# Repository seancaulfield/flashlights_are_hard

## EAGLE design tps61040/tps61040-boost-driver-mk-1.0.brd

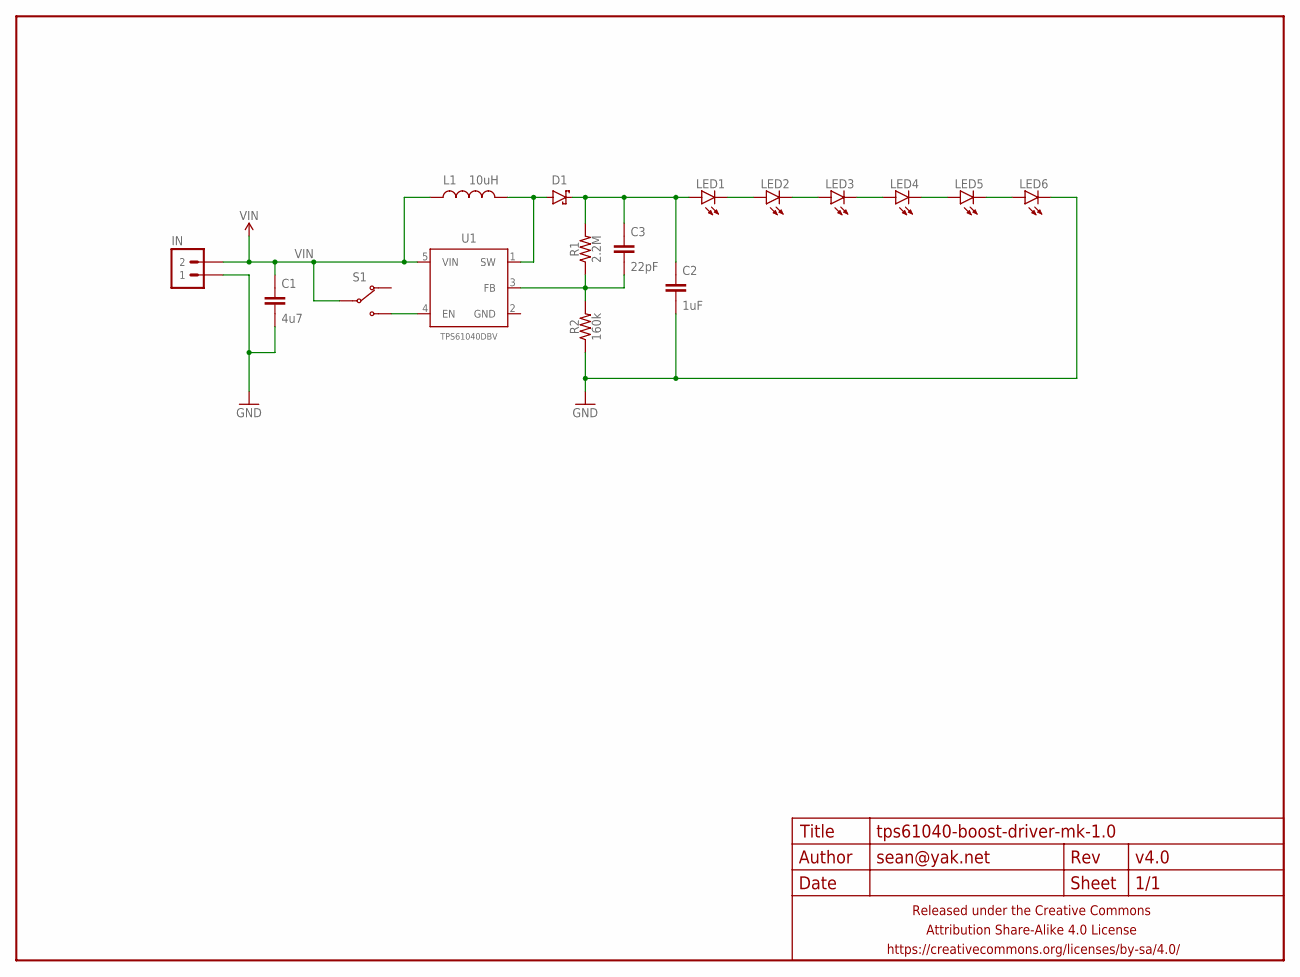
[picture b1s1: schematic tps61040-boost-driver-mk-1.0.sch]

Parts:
C1: 4u7; C0603-TIGHTER
C2: 1uF; C0603-TIGHTER
C3: 22pF; C0603-TIGHTER
D1: DIODE-SCHOTTKYSOD123; SOD123-SCHOTTKY
FRAME1: FRAME-LETTERNO_PACKAGE; DUMMY
IN: M02PTH-CENTERED-R+; 1X02-CENTER-R+
L1: 10uH; L0603
LED1, LED2, LED3, LED4, LED5, LED6: LED5MM_SHORTPADS
R1: 2.2M; R0603-TIGHTER
R2: 160k; R0603-TIGHTER
S1: SWITCH-SPDTSMD-RA; SWITCH-SPDT-SMD-RA
U1: TPS61040DBV; SOT23-5

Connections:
GND: C1.2, C2.2, IN.1, LED6.K (C), R2.1
unnamed: S1.1 (NO), U1.4 (EN)
unnamed: LED1.K (C), LED2.A
unnamed: D1.A, L1.2, U1.1 (SW)
unnamed: C3.2, R1.1, R2.2, U1.3 (FB)
unnamed: LED2.K (C), LED3.A
unnamed: LED3.K (C), LED4.A
unnamed: LED4.K (C), LED5.A
unnamed: LED5.K (C), LED6.A
unnamed: C2.1, C3.1, D1.C, LED1.A, R1.2
VIN: C1.1, IN.2, L1.1, S1.2 (COM), U1.5 (VIN)

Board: 2 copper layers, 17 parts (0 on the bottom side), 11 nets, no tracks yet.

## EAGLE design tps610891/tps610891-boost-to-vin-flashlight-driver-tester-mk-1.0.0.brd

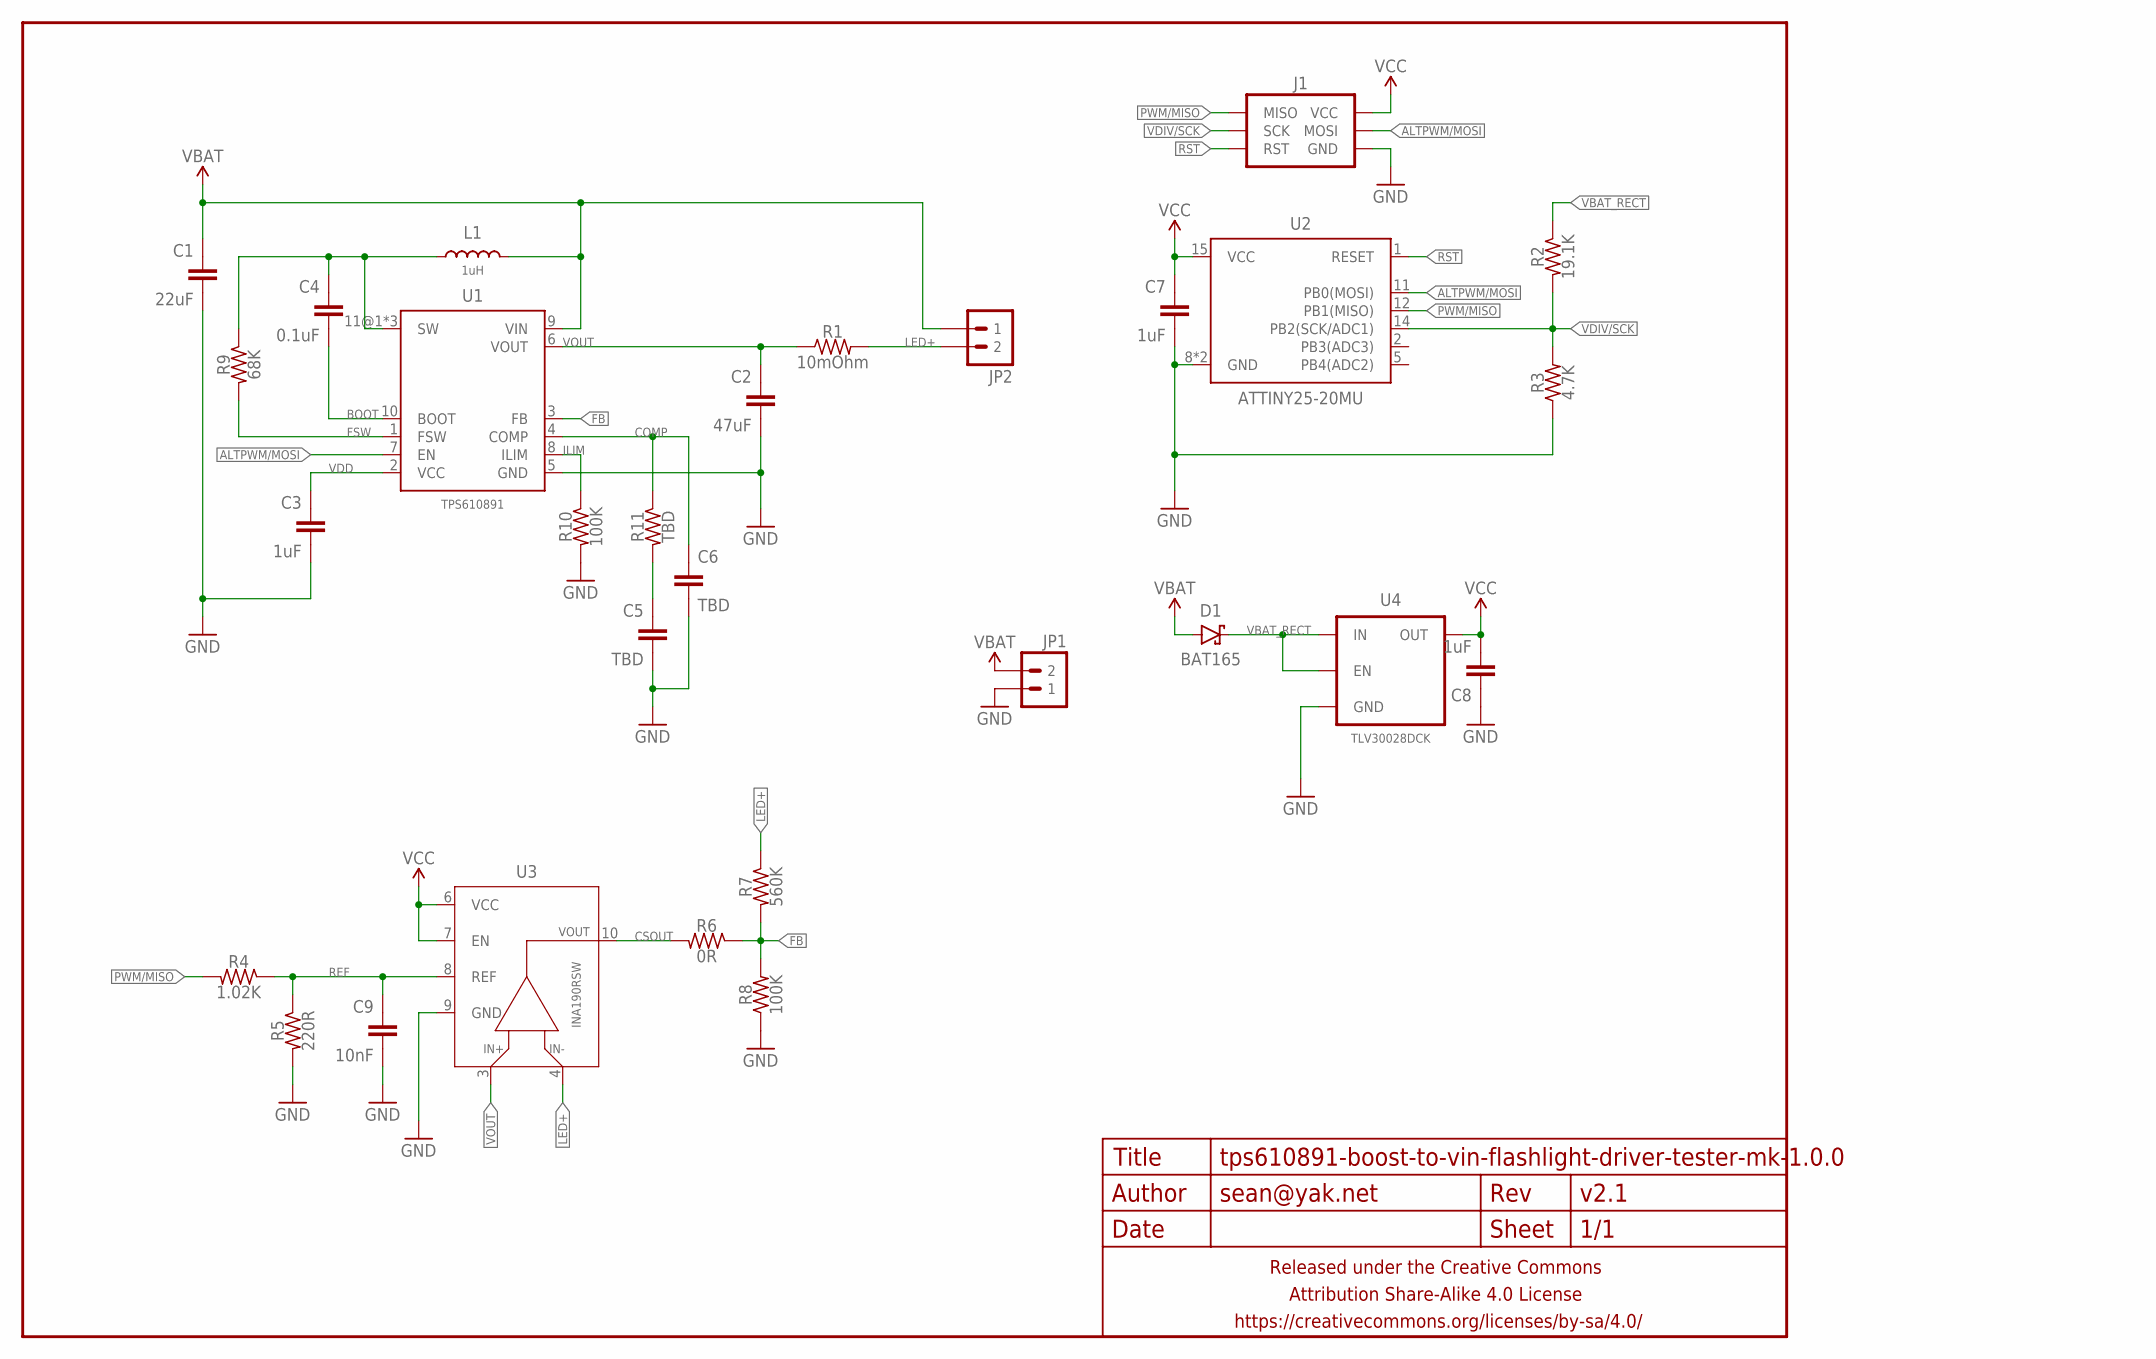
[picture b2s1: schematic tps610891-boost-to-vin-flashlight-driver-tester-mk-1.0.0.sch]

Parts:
C1: 22uF; C1206
C2: 47uF; C1206
C3, C7, C8: 1uF; C0402
C4: 0.1uF; C0402
C5, C6: TBD; C0402
C9: 10nF; C0402
D1: BAT165; SOD323-SCHOTTKY
FRAME1: FRAME-LETTERNO_PACKAGE; DUMMY
J1: AVR_SPI_PRG_6PTH; 2X3
JP1, JP2: M021X02_NO_SILK; 1X02_NO_SILK
L1: 1uH; XAL60XX
R1: 10mOhm; R1206
R2: 19.1K; R0402
R3: 4.7K; R0402
R4: 1.02K; R0402
R5: 220R; R0402
R6: 0R; R0402
R7: 560K; R0402
R8, R10: 100K; R0402
R9: 68K; R0402
R11: TBD; R0402
U1: TPS610891; VQFN-11
U2: ATTINY25-20MU; QFN20
U3: INA190RSW; UQFN-10
U4: TLV30028DCK; SC70

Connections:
ALTPWM/MOSI: J1.4 (MOSI), U1.7 (EN), U2.11 (PB0(MOSI))
BOOT: C4.2, U1.10 (BOOT)
COMP: C6.1, R11.1, U1.4 (COMP)
CSOUT: R6.2, U3.10 (OUT)
FB: R6.1, R7.2, R8.2, U1.3 (FB)
FSW: R9.2, U1.1 (FSW)
GND: C1.2, C2.2, C3.2, C5.2, C6.2, C7.2, C8.1, C9.2, J1.6 (GND), JP1.1, R3.1, R5.2, R8.1, R10.2, U1.5 (GND), U2.8 (GND), U2.PAD (GND), U3.9 (GND), U4.2 (GND)
ILIM: R10.1, U1.8 (ILIM)
LED+: JP2.2, R1.2, R7.1, U3.4 (VIN-)
unnamed: C4.1, L1.P$1 (1), R9.1, U1.11@1 (SW), U1.11@2 (SW), U1.11@3 (SW)
unnamed: C5.1, R11.2
PWM/MISO: J1.1 (MISO), R4.2, U2.12 (PB1(MISO))
REF: C9.1, R4.1, R5.1, U3.8 (REF)
RST: J1.5 (RST), U2.1 (RESET)
VBAT: C1.1, D1.A, JP1.2, JP2.1, L1.P$2 (2), U1.9 (VIN)
VBAT_RECT: D1.C, R2.1, U4.1 (IN), U4.3 (EN)
VCC: C7.1, C8.2, J1.2 (VCC), U2.15 (VCC), U3.6 (VCC), U3.7 (EN), U4.5 (OUT)
VDD: C3.1, U1.2 (VCC)
VDIV/SCK: J1.3 (SCK), R2.2, R3.2, U2.14 (PB2(SCK/ADC1))
VOUT: C2.1, R1.1, U1.6 (VOUT), U3.3 (VIN+)

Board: 2 copper layers, 30 parts (0 on the bottom side), 20 nets, no tracks yet.

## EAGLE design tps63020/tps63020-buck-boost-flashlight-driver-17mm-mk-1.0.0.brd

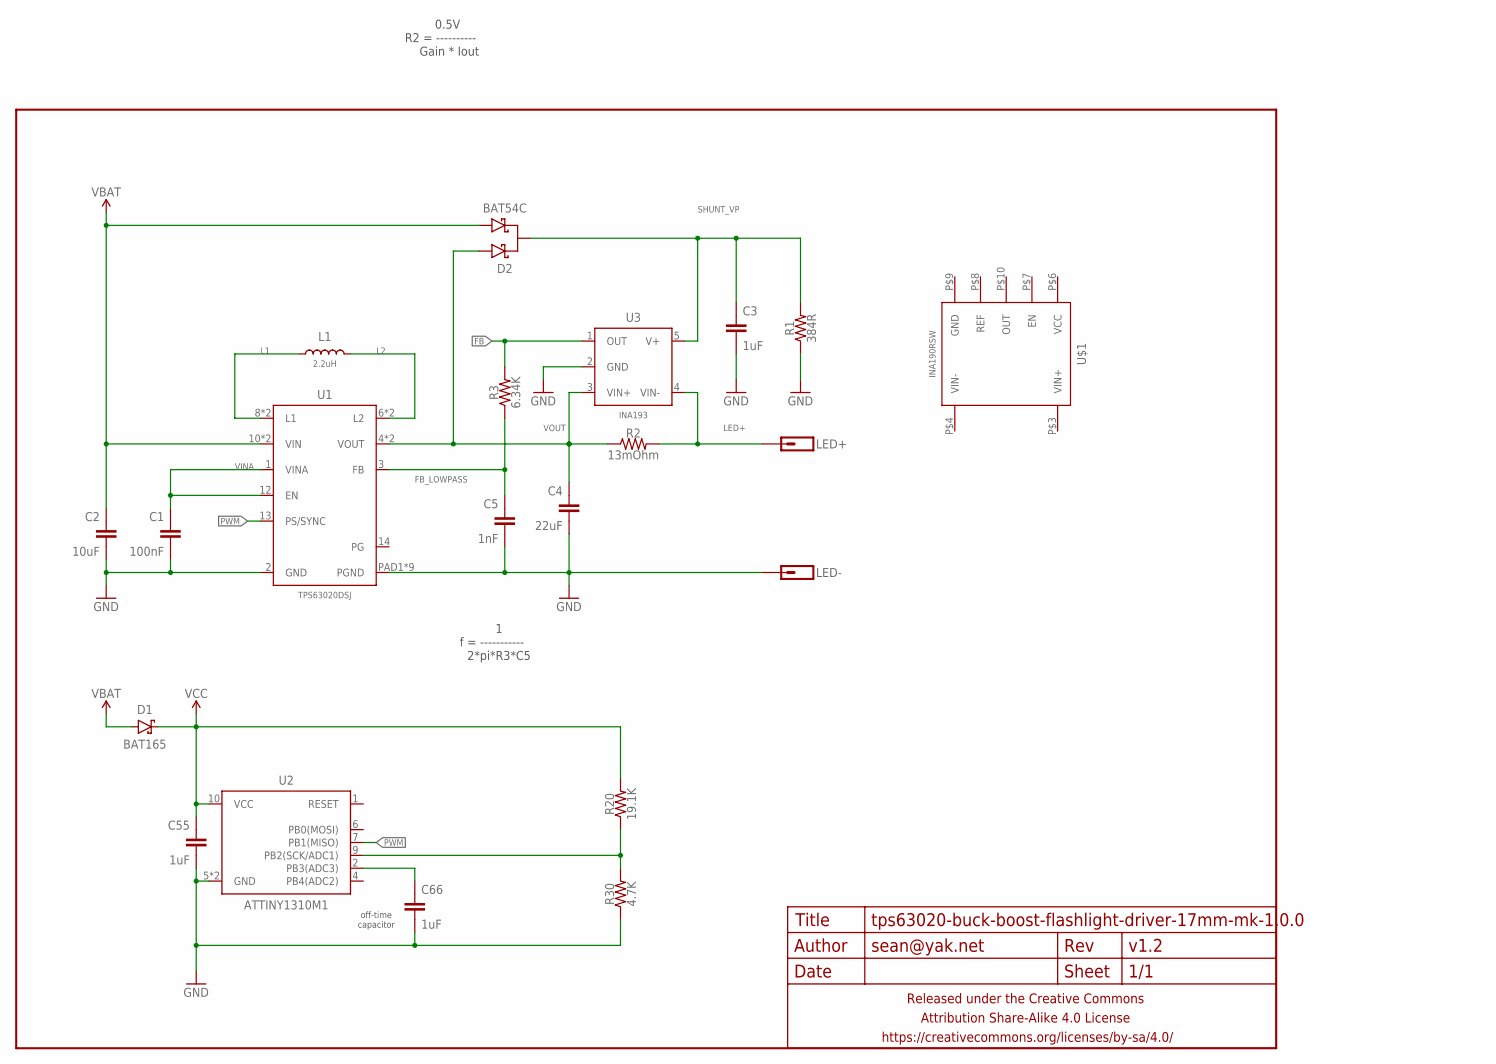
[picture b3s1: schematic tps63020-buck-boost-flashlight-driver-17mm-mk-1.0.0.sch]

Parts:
C1: 100nF; C0402
C2: 10uF; C0603-TIGHTER
C3, C66: 1uF; C0402
C4: 22uF; C0603-TIGHTER
C5: 1nF; C0402
C55: 1uF; C0603-TIGHTER
D1: BAT165; SOD323-SCHOTTKY
D2: BAT54C; SOT23
FRAME1: FRAME-LETTERNO_PACKAGE; DUMMY
L1: 2.2uH; XAL50X0
LED+: M01PTH-1MM-CIR-NS; 1X01-1MM-CIR-NS
LED-: M01PTH-1MM-CIR-NS; 1X01-1MM-CIR-NS
R1: 384R; R0402
R2: 13mOhm; R0805-TIGHTER
R3: 6.34K; R0402
R20: 19.1K; R0603-TIGHTER
R30: 4.7K; R0603-TIGHTER
U1: TPS63020DSJ; VSON-14-4MMX3MM
U2: ATTINY1310M1; QFN10(2X5)
U3: INA193; SOT23-5
U$1: INA190RSW; UQFN-10

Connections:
FB: R3.2, U3.1 (OUT)
FB_LOWPASS: C5.1, R3.1, U1.3 (FB)
GND: C1.2, C2.2, C3.2, C4.2, C5.2, C55.2, C66.2, LED-.1, R1.1, R30.1, U1.2 (GND), U1.PAD1 (PGND), U1.PAD2 (PGND), U1.PAD3 (PGND), U1.PAD4 (PGND), U1.PAD5 (PGND), U1.PAD6 (PGND), U1.PAD7 (PGND), U1.PAD8 (PGND), U1.PADCENTER (PGND), U2.5 (GND), U2.PAD (GND), U3.2 (GND)
L1: L1.P$1 (1), U1.8 (L1), U1.9 (L1)
L2: L1.P$2 (2), U1.6 (L2), U1.7 (L2)
LED+: LED+.1, R2.2, U3.4 (VIN-)
unnamed: R20.1, R30.2, U2.9 (PB2(SCK/ADC1))
unnamed: C66.1, U2.2 (PB3(ADC3))
PWM: U1.13 (PS/SYNC), U2.7 (PB1(MISO))
SHUNT_VP: C3.1, D2.3 (K), R1.2, U3.5 (V+)
VBAT: C2.1, D1.A, D2.2 (A2), U1.10 (VIN), U1.11 (VIN)
VCC: C55.1, D1.C, R20.2, U2.10 (VCC)
VINA: C1.1, U1.1 (VINA), U1.12 (EN)
VOUT: C4.1, D2.1 (A1), R2.1, U1.4 (VOUT), U1.5 (VOUT), U3.3 (VIN+)

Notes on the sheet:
off-time capacitor
1 f = ----------- 2*pi*R3*C5
0.5V R2 = ---------- Gain * Iout

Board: 2 copper layers, 22 parts (2 on the bottom side), 14 nets, no tracks yet.

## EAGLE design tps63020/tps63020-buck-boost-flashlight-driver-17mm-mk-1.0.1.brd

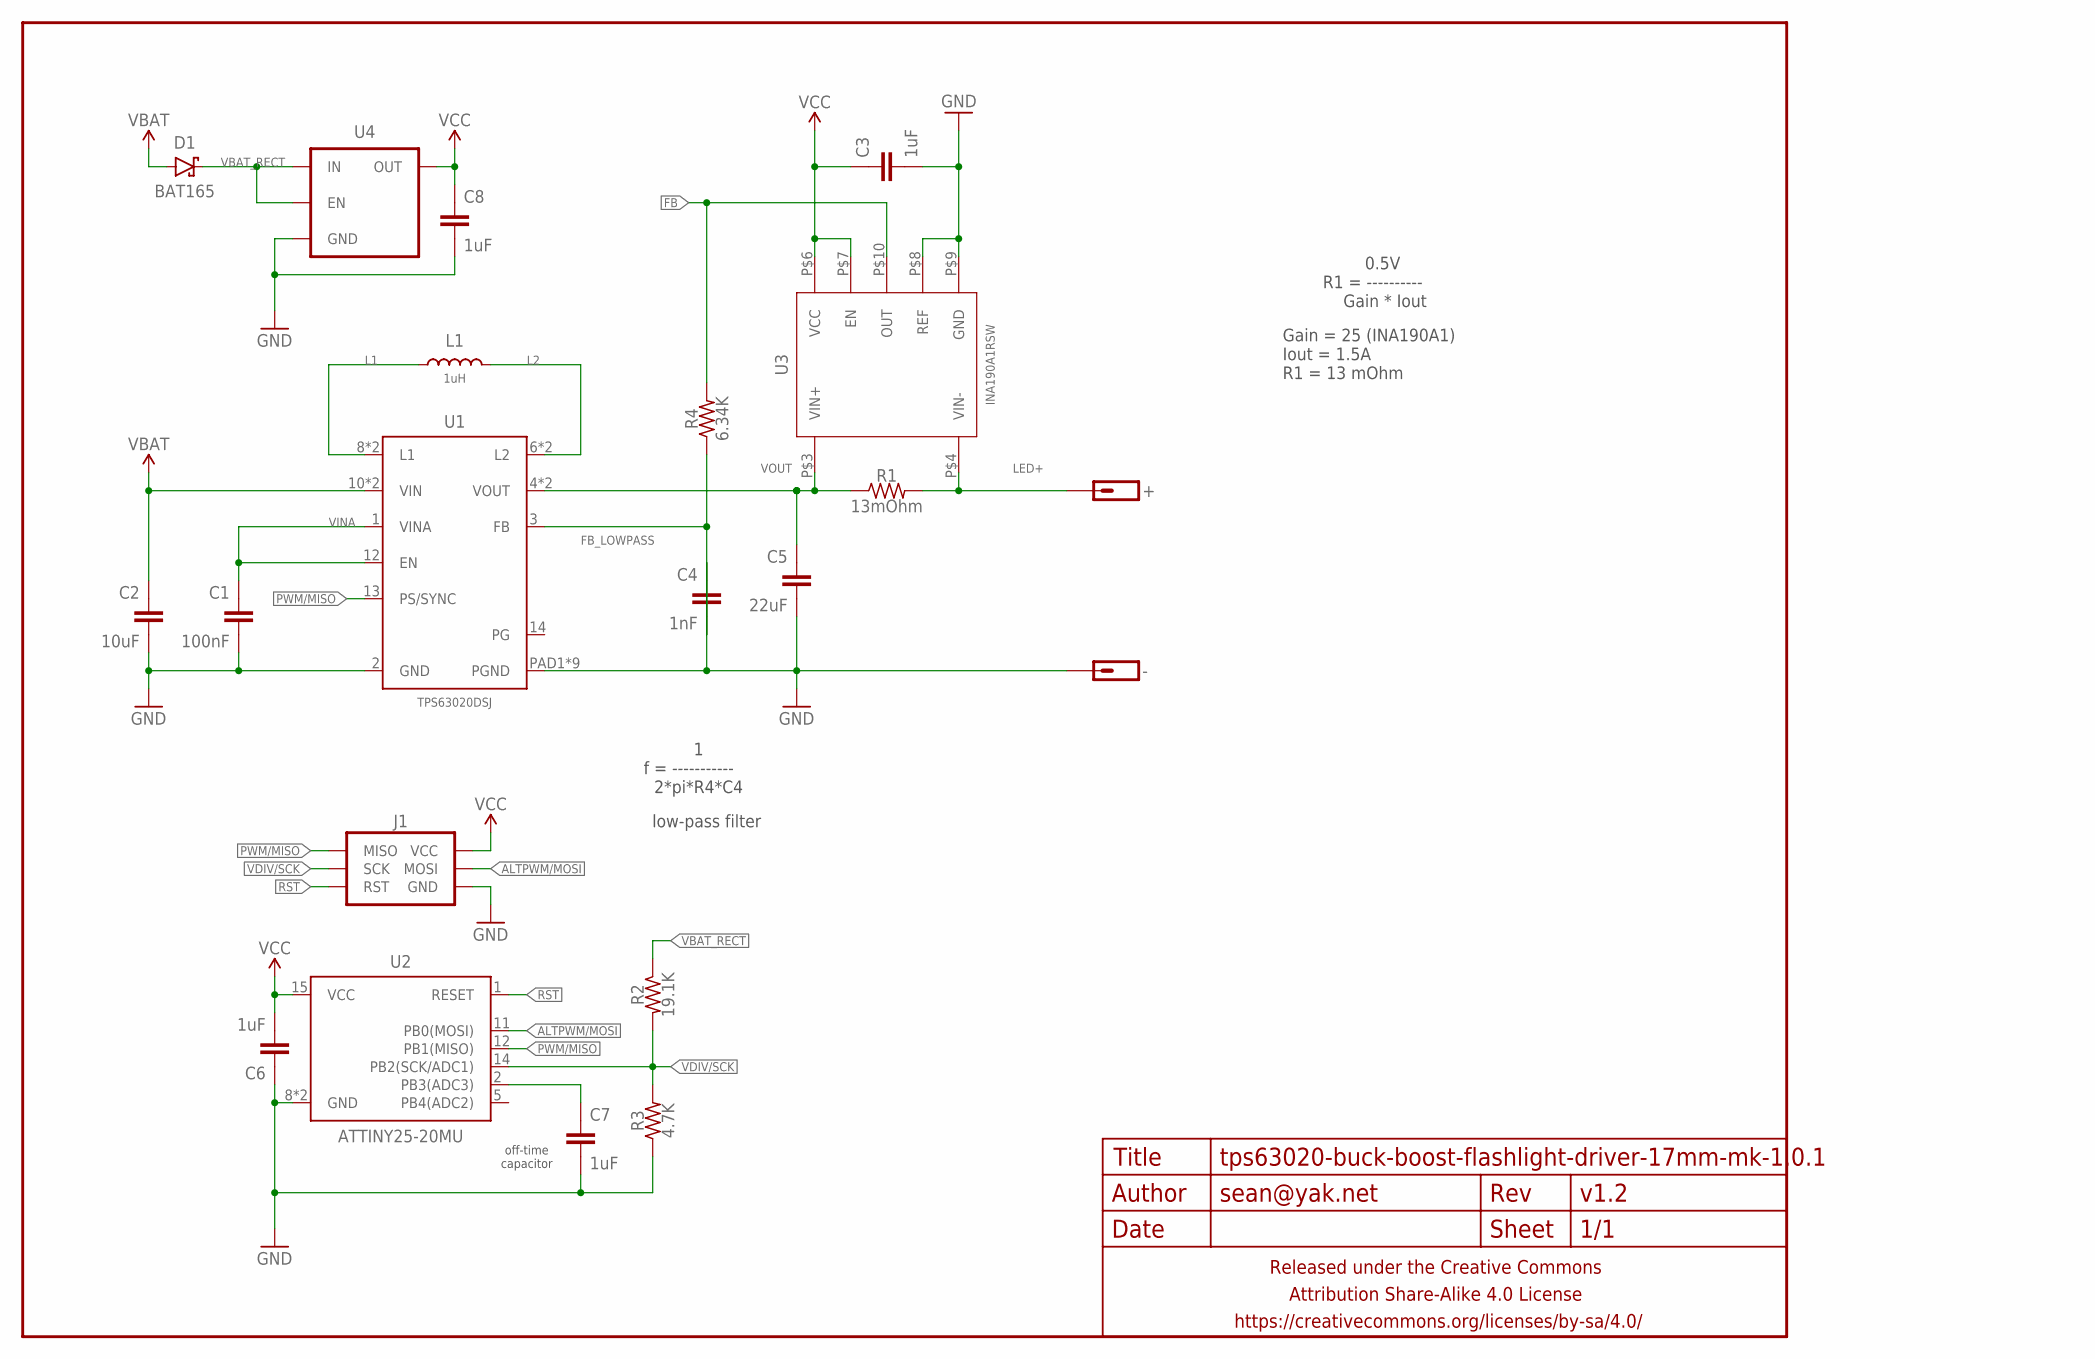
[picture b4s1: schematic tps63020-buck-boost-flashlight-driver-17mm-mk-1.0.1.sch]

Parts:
+: M01PTH-1MM-CIR-NS; 1X01-1MM-CIR-NS
-: M01PTH-1MM-CIR-NS; 1X01-1MM-CIR-NS
C1: 100nF; C0402
C2: 10uF; C0805-TIGHTER
C3, C6, C7, C8: 1uF; C0402
C4: 1nF; C0402
C5: 22uF; C0805-TIGHTER
D1: BAT165; SOD323-SCHOTTKY
FRAME1: FRAME-LETTERNO_PACKAGE; DUMMY
J1: AVR_SPI_PRG_6SMD-1.27MM; 2X3-1.27MM-SMD
L1: 1uH; XAL50X0
R1: 13mOhm; R0805-TIGHTER
R2: 19.1K; R0402
R3: 4.7K; R0402
R4: 6.34K; R0402
U1: TPS63020DSJ; VSON-14-4MMX3MM
U2: ATTINY25-20MU; QFN20
U3: INA190A1RSW; UQFN-10
U4: V_REG_ENTLV700; SC70

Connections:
ALTPWM/MOSI: J1.4 (MOSI), U2.11 (PB0(MOSI))
FB: R4.2, U3.P$10 (OUT)
FB_LOWPASS: C4.2, R4.1, U1.3 (FB)
GND: -.1, C1.2, C2.2, C3.2, C4.1, C5.2, C6.1, C7.2, C8.2, J1.6 (GND), R3.1, U1.2 (GND), U1.PAD1 (PGND), U1.PAD2 (PGND), U1.PAD3 (PGND), U1.PAD4 (PGND), U1.PAD5 (PGND), U1.PAD6 (PGND), U1.PAD7 (PGND), U1.PAD8 (PGND), U1.PADCENTER (PGND), U2.8 (GND), U2.PAD (GND), U3.P$8 (REF), U3.P$9 (GND), U4.2 (GND)
L1: L1.P$1 (1), U1.8 (L1), U1.9 (L1)
L2: L1.P$2 (2), U1.6 (L2), U1.7 (L2)
LED+: +.1, R1.2, U3.P$4 (VIN-)
unnamed: C7.1, U2.2 (PB3(ADC3))
PWM/MISO: J1.1 (MISO), U1.13 (PS/SYNC), U2.12 (PB1(MISO))
RST: J1.5 (RST), U2.1 (RESET)
VBAT: C2.1, D1.A, U1.10 (VIN), U1.11 (VIN)
VBAT_RECT: D1.C, R2.1, U4.1 (IN), U4.3 (EN)
VCC: C3.1, C6.2, C8.1, J1.2 (VCC), U2.15 (VCC), U3.P$6 (VCC), U3.P$7 (EN), U4.5 (OUT)
VDIV/SCK: J1.3 (SCK), R2.2, R3.2, U2.14 (PB2(SCK/ADC1))
VINA: C1.1, U1.1 (VINA), U1.12 (EN)
VOUT: C5.1, R1.1, U1.4 (VOUT), U1.5 (VOUT), U3.P$3 (VIN+)

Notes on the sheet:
off-time capacitor
1 f = ----------- 2*pi*R4*C4
0.5V R1 = ---------- Gain * Iout
low-pass filter
Gain = 25 (INA190A1) Iout = 1.5A R1 = 13 mOhm

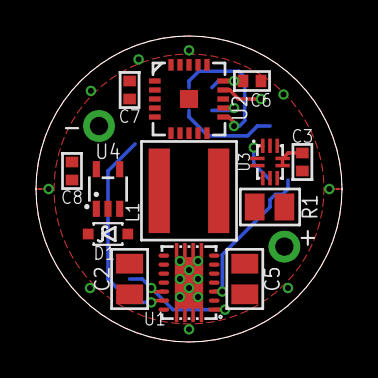
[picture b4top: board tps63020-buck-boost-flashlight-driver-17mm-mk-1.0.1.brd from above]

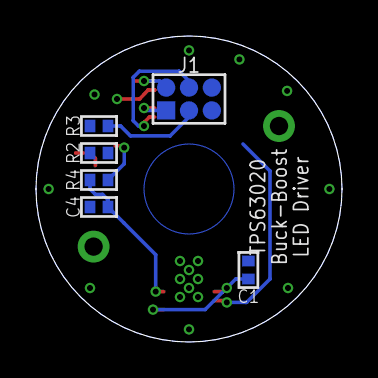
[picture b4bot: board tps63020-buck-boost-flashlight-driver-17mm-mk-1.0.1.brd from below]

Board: 2 copper layers, 17.0 x 17.0 mm, 22 parts (6 on the bottom side), 16 nets.

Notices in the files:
parts and their libraries:
a_parts: Released under the Creative Commons Attribution Share-Alike 4.0 License
a_parts: https://creativecommons.org/licenses/by-sa/4.0
a_parts: Released under the Creative Commons
